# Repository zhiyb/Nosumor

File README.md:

# USB Mix

Design a small USB keyboard for playing [osu!](https://osu.ppy.sh/): [Blog posts](https://zhiyb.wordpress.com/category/cc/embedded/nosumor/)

In addition to mandatory keyboard functionalities, USB audio and Micro SD support are also added. So it's now called USB Mix.

The PCB layout was made compatible with [the original Nosumor v3 casing](http://noodlefighter.com/工作日志/log_nono/), which sells on [the official osu! store](https://osu.ppy.sh/store/product/20).

However, as a hobby project for learning USB framework and achieving high performance, the parts used in this design are probably unnecessarily expensive.

## Features

- USB 2.0 high-speed connection with 8kHz polling rate
- 5 switches (2x Cherry MX switches & 3x tactile switches)
- RGB lighting!
- Audio output through headphone jack using USB audio class 2
- Micro SD card reader
- Application for dynamic reconfiguration and firmware upgrade

### Planned features

- Audio input (MIC) through headphone jack
- MPU-9250 9-axis motion sensor
- ADC waveform capture
- DAC waveform generation

## PCB features

- 50×50 (mm) board area
- 2 mechanical keyboard switches (Cherry MX RGB compatible) and 3 tactile buttons
- Keycap and bottom-side RGB lighting
- STM32F722RE Cortex-M7 high performance MCU @216MHz
- USB 2.0 high-speed PHY USB3370
- 3.5mm audio jack with TLV320AIC3110 audio codec
- InvenSense MPU-9250 9-axis motion sensor
- On-board FT2232D connected to UART & JTAG for debugging
- Test points for 2xADC & 1xDAC
- Extension UART port with 3.3V power

Gerber files for PCB manufacturer Seeed Studio provided.

## Estimated costs

Configuration | Cost
---|---
Basic keyboard | £20
With audio and Micro SD slot | £30
Also with debugging USB port | £38

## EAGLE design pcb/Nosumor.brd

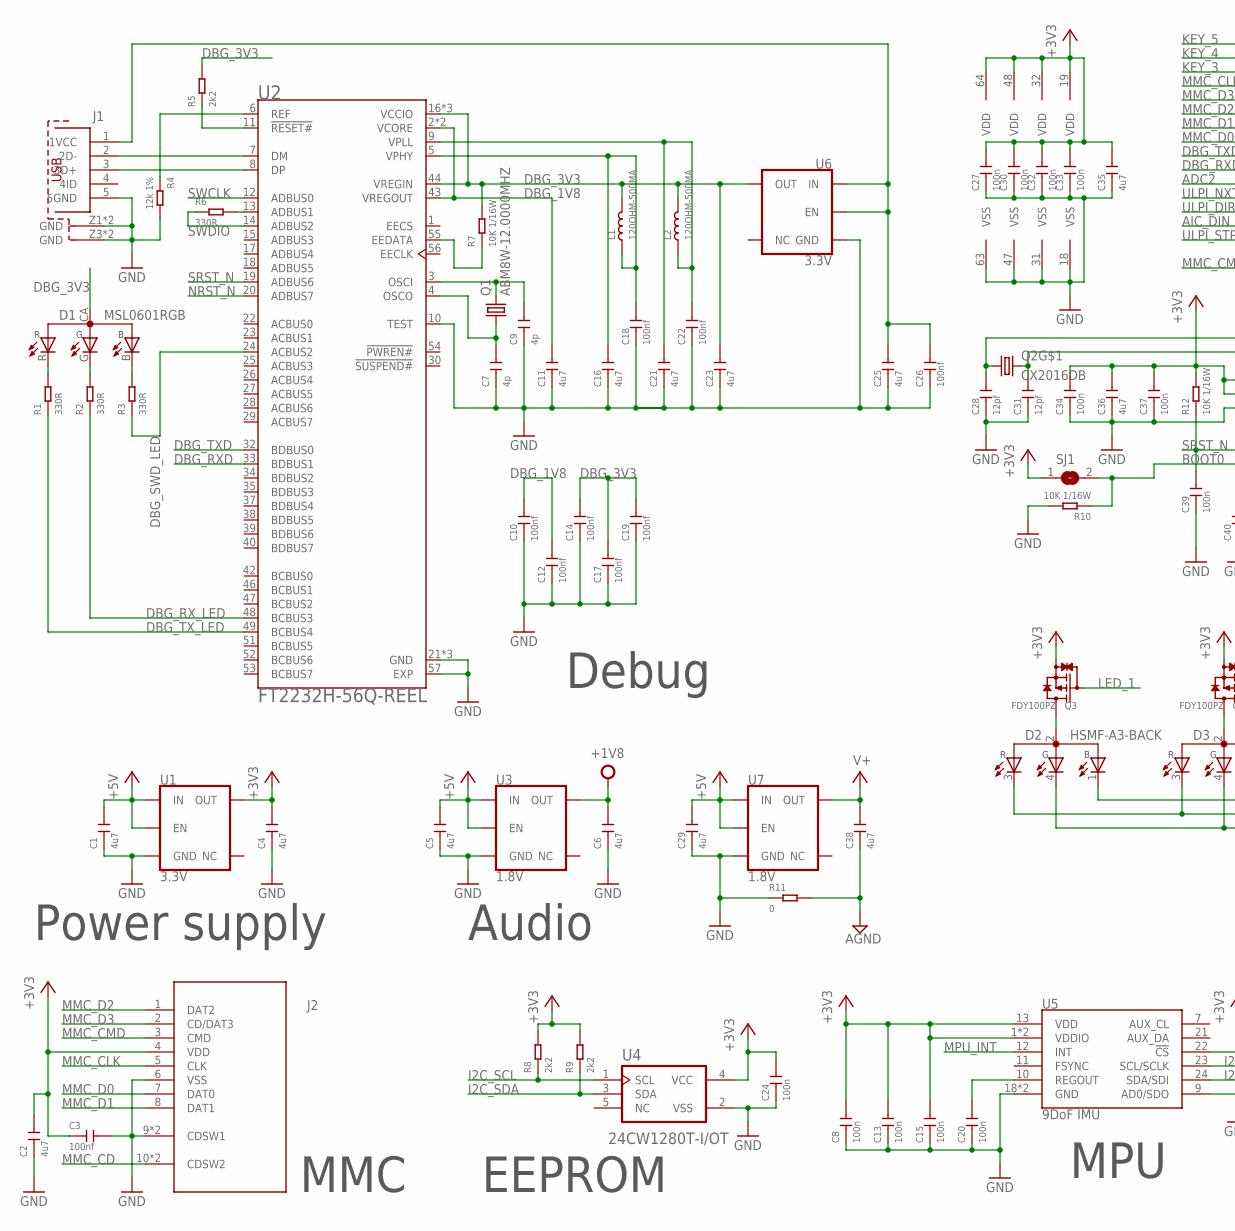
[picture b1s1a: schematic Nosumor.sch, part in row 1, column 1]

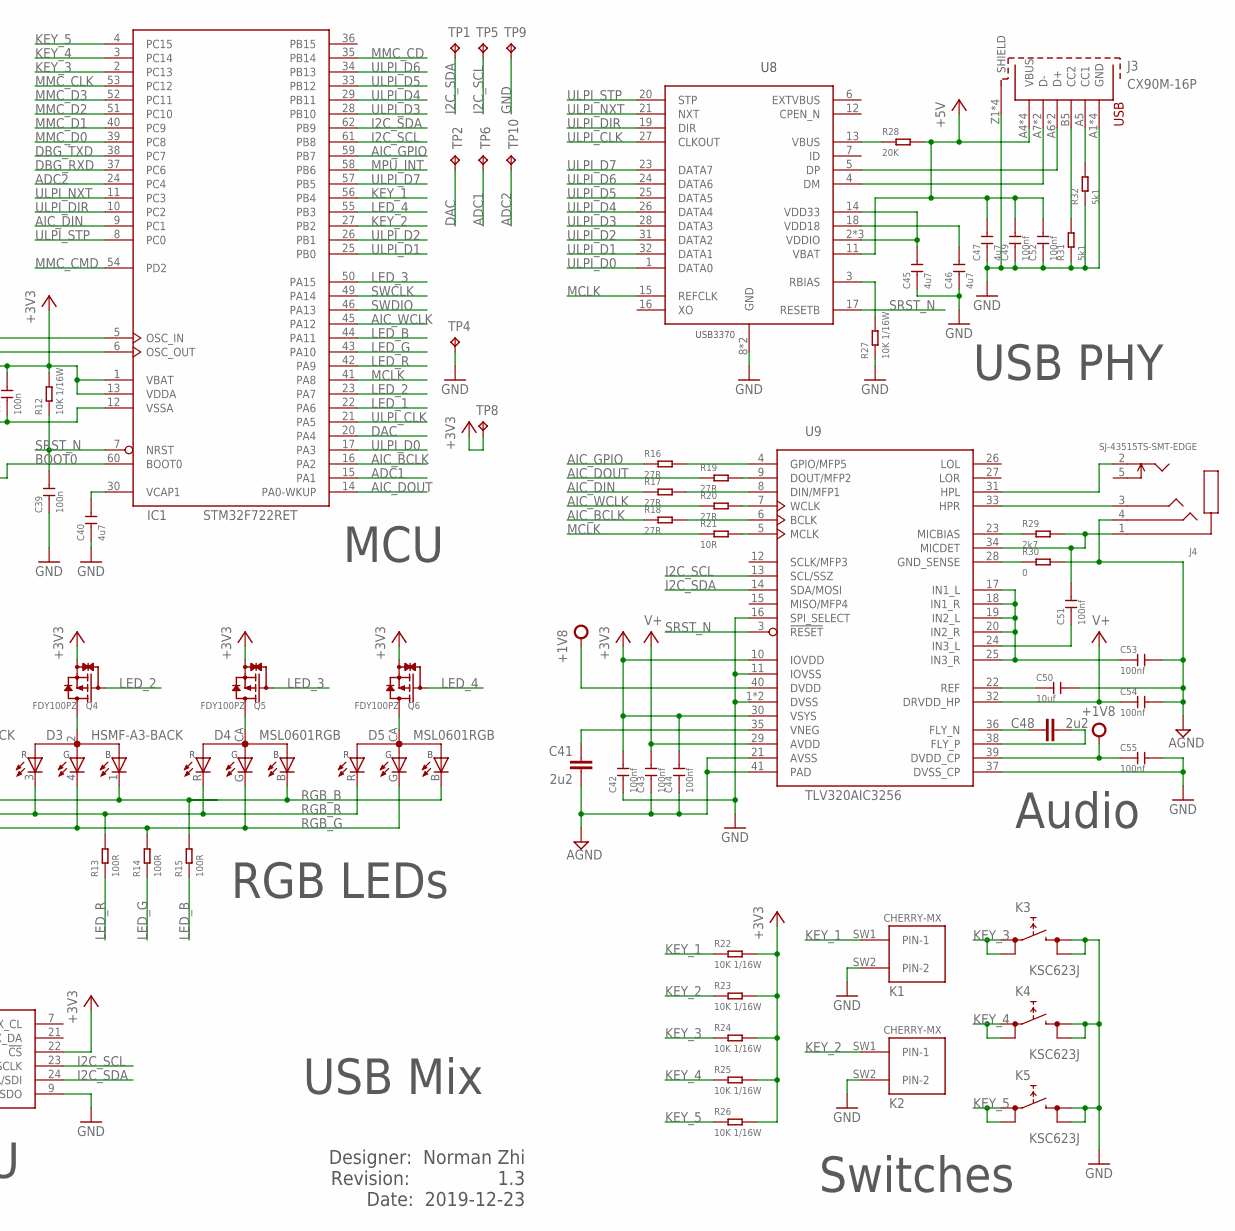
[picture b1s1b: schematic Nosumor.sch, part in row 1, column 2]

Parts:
C1, C2, C4, C5, C6, C11, C16, C21, C23, C25, C29, C38, C45, C46, C47: 4u7; C0402
C3, C10, C12, C14, C17, C18, C19, C22, C26, C42, C43, C44, C49, C51, C52, C53, C54, C55: 100nf; C0402
C7, C9: 4p; C0402
C8, C13, C15, C20, C24, C27, C30, C32, C33, C34, C37, C39: 100n; C0402
C28, C31: 12pf; C0402
C35, C36, C40: 4u7; C0603
C41, C48: 2u2; C0603K
C50: 10uf; C0603
D1, D4, D5: MSL0601RGB; 1105
D2, D3: HSMF-A3-BACK
IC1: STM32F722RET; LQFP64
J1: 629105150521
J2: 693071010811
J3: CX90M-16P
J4: SJ-43515TS-SMT-EDGE; SJ-4351*-SMT-MIRRORED-EDGE
K1, K2: CHERRY-MX
K3, K4, K5: KSC623J; KSC-J
L1, L2: 120OHM-500MA; L0603
Q1: ABM8W-12.0000MHZ; ABM8W
Q2: CX2016DB
Q3, Q4, Q5, Q6: FDY100PZ; SC-89
R1, R2, R3, R6: 330R; R0402
R4: 12k 1%; R0402
R5, R8, R9: 2k2; R0402
R7, R10, R12, R22, R23, R24, R25, R26, R27: 10K 1/16W; R0402
R11, R30: 0; R0402
R13, R14, R15: 100R; R0402
R16, R17, R18, R19, R20: 27R; R0402
R21: 10R; R0402
R28: 20K; R0402
R29: 2k7; R0402
R31, R32: 5k1; R0402
SJ1: SJ
TP1, TP2, TP4, TP5, TP6, TP8, TP9, TP10: TPB1,27; B1,27
U1, U6: 3.3V; SOT23-5
U2: FT2232H-56Q-REEL; QFN50P800X800X100-57N
U3, U7: 1.8V; SOT23-5
U4: 24CW1280T-I/OT; SOT95P280X145-5N
U5: 9DoF IMU; QFN24-3X3
U8: USB3370; QFN32
U9: TLV320AIC3256; QFN40P500X500X80-41N

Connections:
+1V8: C6.2, C55.1, U3.5 (OUT), U9.39 (DVDD_CP), U9.40 (DVDD)
+3V3: C2.2, C3.1, C4.2, C8.2, C13.2, C15.2, C24.2, C27.2, C30.2, C32.2, C33.2, C34.2, C35.2, C36.2, C37.2, C42.2, C44.2, IC1.1 (VBAT), IC1.13 (VDDA), IC1.19 (VDD), IC1.32 (VDD), IC1.48 (VDD), IC1.64 (VDD), J2.4 (VDD), Q3.3 (S), Q4.3 (S), Q5.3 (S), Q6.3 (S), R8.2, R9.2, R12.2, R22.2, R23.2, R24.2, R25.2, R26.2, SJ1.1, TP8.TP, U1.5 (OUT), U4.4 (VCC), U5.1 (VDDIO), U5.8 (VDDIO), U5.13 (VDD), U5.22 (!CS), U9.10 (IOVDD), U9.30 (VSYS)
+5V: C1.2, C5.2, C29.2, C47.2, C49.2, C52.2, J3.A4 (VBUS), J3.A9 (VBUS), J3.B4 (VBUS), J3.B9 (VBUS), R28.2, U1.1 (IN), U1.3 (EN), U3.1 (IN), U3.3 (EN), U7.1 (IN), U7.3 (EN), U8.11 (VBAT)
ADC1: IC1.15 (PA1), TP6.TP
ADC2: IC1.24 (PC4), TP10.TP
AGND: C38.1, C41.2, C43.1, C44.1, C50.2, C53.2, C54.2, J4.4, R11.2, R30.2, U9.21 (AVSS), U9.41 (PAD)
AIC_BCLK: IC1.16 (PA2), R18.1
AIC_BCLK_R: R18.2, U9.6 (BCLK)
AIC_DIN: IC1.9 (PC1), R17.1
AIC_DIN_R: R17.2, U9.8 (DIN/MFP1)
AIC_DOUT: IC1.14 (PA0-WKUP), R19.1
AIC_DOUT_R: R19.2, U9.9 (DOUT/MFP2)
AIC_GPIO: IC1.59 (PB7), R16.1
AIC_GPIO_R: R16.2, U9.4 (GPIO/MFP5)
AIC_MCLK_R: R21.2, U9.5 (MCLK)
AIC_WCLK: IC1.45 (PA12), R20.1
AIC_WCLK_R: R20.2, U9.7 (WCLK)
AVDD: C38.2, C43.2, C54.1, U7.5 (OUT), U9.29 (AVDD), U9.32 (DRVDD_HP)
BOOT0: IC1.60 (BOOT0), R10.1, SJ1.2
DAC: IC1.20 (PA4), TP2.TP
DBG_1V8: C10.2, C11.2, C12.2, U2.2 (VCORE), U2.31 (VCORE), U2.43 (VREGOUT)
DBG_3V3: C14.2, C17.2, C19.2, C23.2, D1.CA (A), L1.2, L2.2, R5.2, R7.2, U2.16 (VCCIO), U2.36 (VCCIO), U2.44 (VREGIN), U2.50 (VCCIO), U6.5 (OUT)
DBG_DM: J1.2 (2D-), U2.7 (DM)
DBG_DP: J1.3 (3D+), U2.8 (DP)
DBG_RXD: IC1.37 (PC6), U2.33 (BDBUS1)
DBG_RX_LED: R2.1, U2.48 (BCBUS3)
DBG_SWD_LED: R3.1, U2.24 (ACBUS2)
DBG_TXD: IC1.38 (PC7), U2.32 (BDBUS0)
DBG_TX_LED: R1.1, U2.49 (BCBUS4)
GND: C1.1, C2.1, C3.2, C4.1, C5.1, C6.1, C7.1, C8.1, C9.1, C10.1, C11.1, C12.1, C13.1, C14.1, C15.1, C16.1, C17.1, C18.1, C19.1, C20.1, C21.1, C22.1, C23.1, C24.1, C25.1, C26.1, C27.1, C28.1, C29.1, C30.1, C31.1, C32.1, C33.1, C34.1, C35.1, C36.1, C37.1, C39.1, C40.1, C42.1, C45.1, C46.1, C47.1, C49.1, C52.1, C55.2, IC1.12 (VSSA), IC1.18 (VSS), IC1.31 (VSS), IC1.47 (VSS), IC1.63 (VSS), J1.5 (5GND), J1.Z1 (GND), J1.Z2 (GND), J1.Z3 (GND), J1.Z4 (GND), J2.6 (VSS), J2.9 (CDSW1), J2.9-1 (CDSW1), J3.A1 (GND), J3.A12 (GND), J3.B1 (GND), J3.B12 (GND), J3.Z1 (SHIELD), J3.Z2 (SHIELD), J3.Z3 (SHIELD), J3.Z4 (SHIELD), K1.SW2 (PIN-2), K2.SW2 (PIN-2), K3.2, K3.4 (2), K4.2, K4.4 (2), K5.2, K5.4 (2), Q2.2 (GND), R4.2, R10.2, R11.1, R27.1, R31.1, R32.1, TP4.TP, TP9.TP, U1.2 (GND), U2.10 (TEST), U2.21 (GND), U2.41 (GND), U2.45 (GND), U2.57 (EXP), U3.2 (GND), U4.2 (VSS), U5.9 (AD0/SDO), U5.18 (GND), U5.20 (GND), U6.2 (GND), U7.2 (GND), U8.8 (GND), U8.EXP (GND), U9.1 (DVSS), U9.2 (DVSS), U9.11 (IOVSS), U9.16 (SPI_SELECT), U9.37 (DVSS_CP)
I2C_SCL: IC1.61 (PB8), R8.1, TP5.TP, U4.1 (SCL), U5.23 (SCL/SCLK), U9.13 (SCL/SSZ)
I2C_SDA: IC1.62 (PB9), R9.1, TP1.TP, U4.3 (SDA), U5.24 (SDA/SDI), U9.14 (SDA/MOSI)
KEY_1: IC1.56 (PB4), K1.SW1 (PIN-1), R22.1
KEY_2: IC1.27 (PB2), K2.SW1 (PIN-1), R23.1
KEY_3: IC1.2 (PC13), K3.1, K3.3 (1), R24.1
KEY_4: IC1.3 (PC14), K4.1, K4.3 (1), R25.1
KEY_5: IC1.4 (PC15), K5.1, K5.3 (1), R26.1
LED_1: IC1.22 (PA6), Q3.1 (G)
LED_2: IC1.23 (PA7), Q4.1 (G)
LED_3: IC1.50 (PA15), Q5.1 (G)
LED_4: IC1.55 (PB3), Q6.1 (G)
LED_B: IC1.44 (PA11), R15.1
LED_G: IC1.43 (PA10), R14.1
LED_R: IC1.42 (PA9), R13.1
MCLK: IC1.41 (PA8), R21.1, U8.15 (REFCLK)
MMC_CD: IC1.35 (PB14), J2.10 (CDSW2), J2.10-1 (CDSW2)
MMC_CLK: IC1.53 (PC12), J2.5 (CLK)
MMC_CMD: IC1.54 (PD2), J2.3 (CMD)
MMC_D0: IC1.39 (PC8), J2.7 (DAT0)
MMC_D1: IC1.40 (PC9), J2.8 (DAT1)
MMC_D2: IC1.51 (PC10), J2.1 (DAT2)
MMC_D3: IC1.52 (PC11), J2.2 (CD/DAT3)
MPU_INT: IC1.58 (PB6), U5.12 (INT)
unnamed: J3.A5 (CC1), R32.2
unnamed: J3.A7 (D-), J3.B7 (D-), U8.4 (DM)
unnamed: J3.A6 (D+), J3.B6 (D+), U8.5 (DP)
unnamed: J3.B5 (CC2), R31.2
unnamed: C9.2, Q1.P$3 (2), U2.3 (OSCI)
unnamed: C7.2, Q1.P$1 (1), U2.4 (OSCO)
unnamed: C51.1, U9.24 (IN3_L)
unnamed: D4.CA (A), Q5.2 (D)
unnamed: J4.3, U9.33 (HPR)
unnamed: J4.2, U9.31 (HPL)
unnamed: R7.1, U2.55 (EEDATA)
unnamed: D1.R (KR), R1.2
unnamed: C51.2, J4.1, R29.2, U9.34 (MICDET)
unnamed: R29.1, U9.23 (MICBIAS)
unnamed: R30.1, U9.28 (GND_SENSE)
unnamed: C53.1, U9.17 (IN1_L), U9.18 (IN1_R), U9.19 (IN2_L), U9.20 (IN2_R), U9.25 (IN3_R)
unnamed: C50.1, U9.22 (REF)
unnamed: C48.1, U9.36 (FLY_N)
unnamed: C28.2, IC1.5 (OSC_IN), Q2.1
unnamed: C48.2, U9.38 (FLY_P)
unnamed: C31.2, IC1.6 (OSC_OUT), Q2.3 (2)
unnamed: D5.CA (A), Q6.2 (D)
unnamed: C40.2, IC1.30 (VCAP1)
unnamed: D1.G (KG), R2.2
unnamed: R28.1, U8.13 (VBUS)
unnamed: D2.2 (A), Q3.2 (D)
unnamed: R27.2, U8.3 (RBIAS)
unnamed: C41.1, U9.35 (VNEG)
unnamed: D3.2 (A), Q4.2 (D)
unnamed: D1.B (KB), R3.2
unnamed: C25.2, C26.2, J1.1 (1VCC), U6.1 (IN), U6.3 (EN)
unnamed: C20.2, U5.10 (REGOUT)
unnamed: R4.1, U2.6 (REF)
unnamed: R5.1, U2.11 (!RESET#)
unnamed: C16.2, C18.2, L1.1, U2.5 (VPHY)
unnamed: C21.2, C22.2, L2.1, U2.9 (VPLL)
unnamed: R6.2, U2.13 (ADBUS1)
NRST_N: U2.20 (ADBUS7)
RGB_B: D2.1 (KB), D3.1 (KB), D4.B (KB), D5.B (KB), R15.2
RGB_G: D2.4 (KG), D3.4 (KG), D4.G (KG), D5.G (KG), R14.2
RGB_R: D2.3 (KR), D3.3 (KR), D4.R (KR), D5.R (KR), R13.2
SRST_N: C39.2, IC1.7 (NRST), R12.1, U2.19 (ADBUS6), U8.17 (RESETB), U9.3 (!RESET)
SWCLK: IC1.49 (PA14), U2.12 (ADBUS0)
SWDIO: IC1.46 (PA13), R6.1, U2.14 (ADBUS2)
ULPI_CLK: IC1.21 (PA5), U8.27 (CLKOUT)
ULPI_D0: IC1.17 (PA3), U8.1 (DATA0)
ULPI_D1: IC1.25 (PB0), U8.32 (DATA1)
ULPI_D2: IC1.26 (PB1), U8.31 (DATA2)
ULPI_D3: IC1.28 (PB10), U8.28 (DATA3)
ULPI_D4: IC1.29 (PB11), U8.26 (DATA4)
ULPI_D5: IC1.33 (PB12), U8.25 (DATA5)
ULPI_D6: IC1.34 (PB13), U8.24 (DATA6)
ULPI_D7: IC1.57 (PB5), U8.23 (DATA7)
ULPI_DIR: IC1.10 (PC2), U8.19 (DIR)
ULPI_NXT: IC1.11 (PC3), U8.21 (NXT)
ULPI_STP: IC1.8 (PC0), U8.20 (STP)
VUSB18: C46.2, U8.18 (VDD18)
VUSB33: C45.2, U8.2 (VDDIO), U8.14 (VDD33), U8.22 (VDDIO), U8.30 (VDDIO)

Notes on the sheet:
Debug
Switches
Power supply
MMC
USB PHY
Audio
MCU
RGB LEDs
MPU
EEPROM
Designer: Norman Zhi Revision: 1.3 Date: 2019-12-23
USB Mix

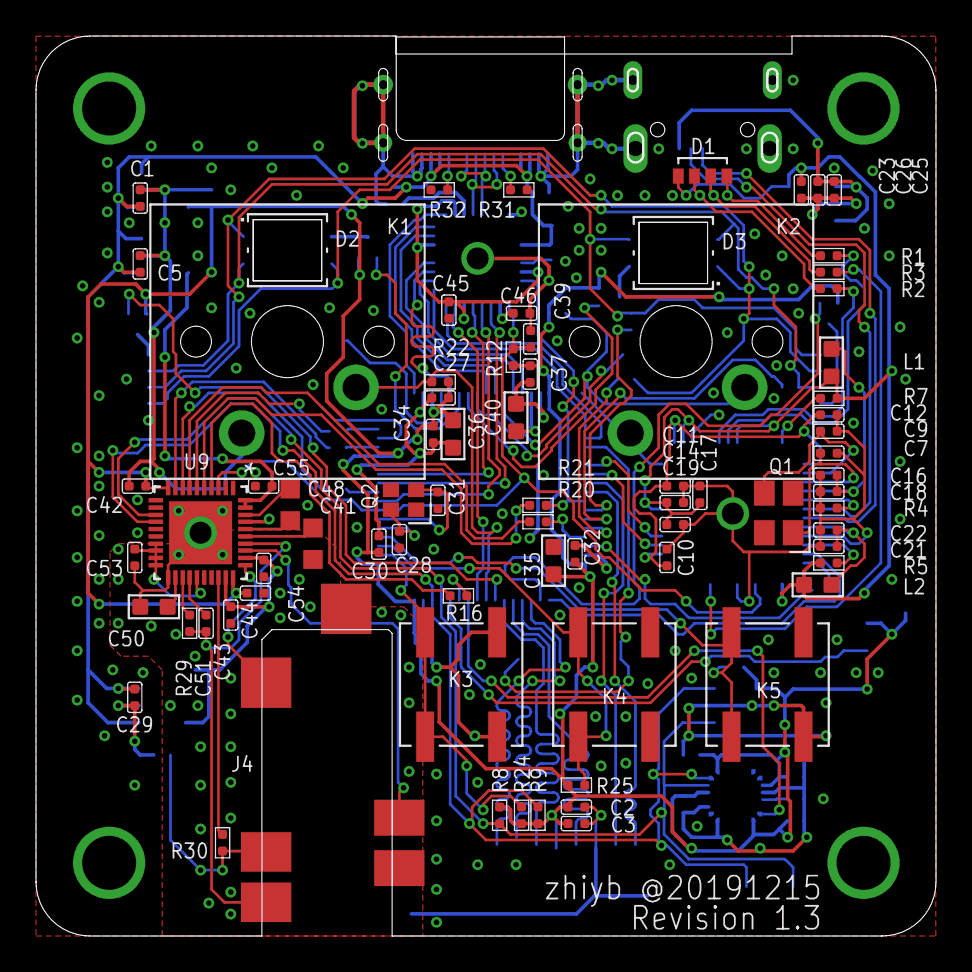
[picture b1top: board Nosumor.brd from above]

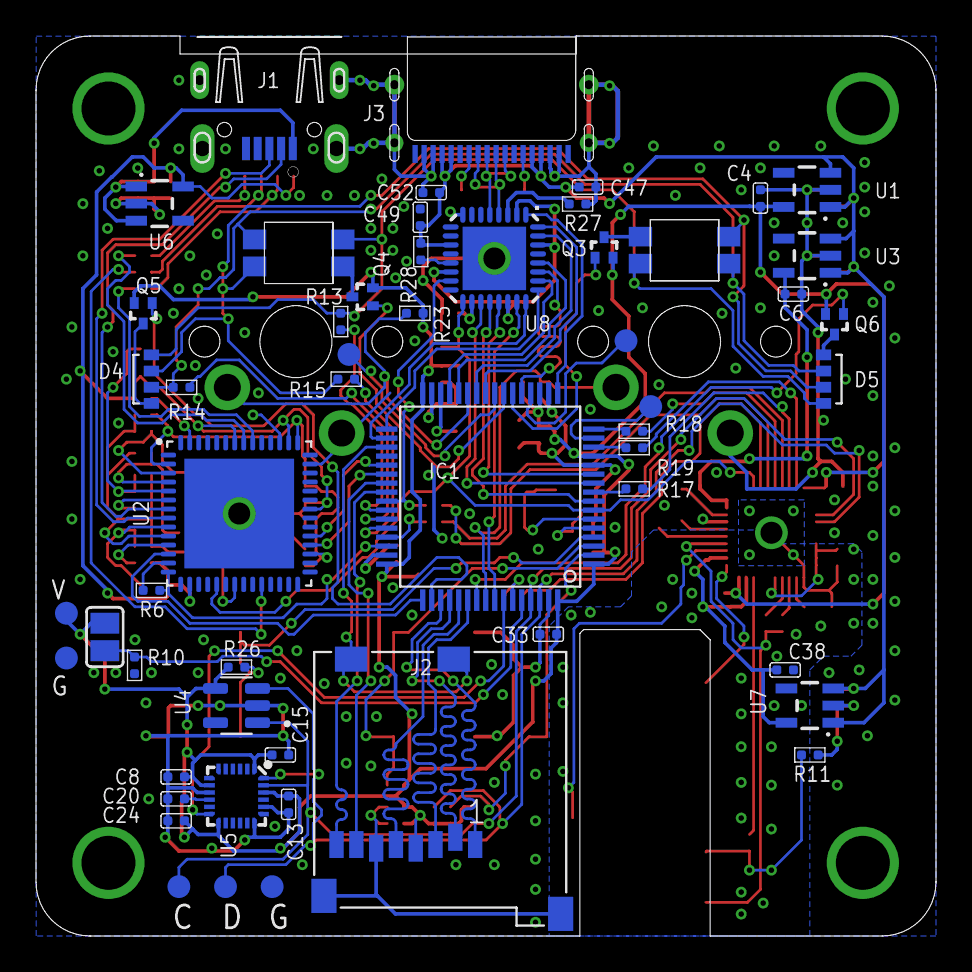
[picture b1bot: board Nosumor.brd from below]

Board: 2 copper layers, 50.0 x 50.0 mm, 128 parts (52 on the bottom side), 110 nets.

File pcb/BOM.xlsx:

Section | Type | Value | Designator | Part # | Quantity | Unit Price | Link
Audio | Capacitor | 100n | C42, C43, C44, C51, C53, C54, C55 | CC0402KRX7R7BB104 | 7 | 8.9999999999999993E-3 | https://www.mouser.co.uk/ProductDetail/603-CC402KRX7R7BB104
Audio | Capacitor | 10u | C50 | GRM188R60J106ME47D | 1 | 0.218 | https://www.mouser.co.uk/productdetail/81-grm188r60j106me47
Audio | Capacitor | 2u2 | C41, C48 | C1608X7R1A225K080AC | 2 | 0.14799999999999999 | https://www.mouser.co.uk/ProductDetail/810-C1608X7R1A225K
Audio | Capacitor | 4u7 | C5, C6, C29, C38 | GRM155R61A475MEAAD | 4 | 6.6000000000000003E-2 | https://www.mouser.co.uk/ProductDetail/81-GRM155R61A475MEAD
Audio | Connector | 3.5mm Jack | J4 | SJ-43515TS-SMT-TR | 1 | 0.81599999999999995 | https://www.mouser.co.uk/ProductDetail/490-SJ43515TS-SMT-TR
Audio | IC | AP2112K-1.8V | U3, U7 | AP2112K-1.8TRG1 | 2 | 0.25 | https://www.mouser.co.uk/ProductDetail/621-AP2112K-1.8TRG1
Audio | IC | TLV320AIC3256 | U9 | TLV320AIC3256IRSBT | 1 | 8.5299999999999994 | https://www.mouser.co.uk/ProductDetail/595-V320AIC3256IRSBT
Audio | Resistor | 0R | R11, R30 | RC0402FR-070RL | 2 | 3.0000000000000001E-3 | https://www.mouser.co.uk/ProductDetail/603-RC0402FR-070RL
Audio | Resistor | 10R | R21 | RC0402FR-0710RL | 1 | 4.0000000000000001E-3 | https://www.mouser.co.uk/ProductDetail/Yageo/RC0402FR-0710RL
Audio | Resistor | 27R | R16, R17, R18, R19, R20 | RC0402FR-0727RL | 5 | 3.0000000000000001E-3 | https://www.mouser.co.uk/ProductDetail/603-RC0402FR-0727RL
Audio | Resistor | 2k7 | R29 | RC0402FR-072K7L | 1 | 3.0000000000000001E-3 | https://www.mouser.co.uk/ProductDetail/603-RC0402FR-072K7L
Basic | Capacitor | 100n | C27, C30, C32, C33, C34, C37, C39, C49, C52 | CC0402KRX7R7BB104 | 9 | 8.9999999999999993E-3 | https://www.mouser.co.uk/ProductDetail/603-CC402KRX7R7BB104
Basic | Capacitor | 12p | C28, C31 | GRM1555C1H120JA01D | 2 | 3.1E-2 | https://www.mouser.co.uk/productdetail/81-grm1555c1h120ja1d
Basic | Capacitor | 4u7 | C1, C4, C35, C36, C40, C45, C46, C47 | GRM155R61A475MEAAD | 8 | 6.6000000000000003E-2 | https://www.mouser.co.uk/ProductDetail/81-GRM155R61A475MEAD
Basic | Connector | USB Type-C | J3 | CX90M-16P | 1 | 1.75 | https://www.mouser.co.uk/ProductDetail/798-CX90M-16P
Basic | Crystal | 19.2M | Q2 | CX2016DB19200H0FLJC2 | 1 | 0.46100000000000002 | https://www.mouser.co.uk/ProductDetail/581-CX2016DB19200HLJ
Basic | IC | AP2112K-3.3V | U1 | AP2112K-3.3TRG1 | 1 | 0.25 | https://www.mouser.co.uk/ProductDetail/621-AP2112K-3.3TRG1
Basic | IC | STM32F722 | IC1 | STM32F722RET6 | 1 | 7.9 | https://www.mouser.co.uk/ProductDetail/511-STM32F722RET6
Basic | IC | USB3370B | U8 | USB3370B-EZK-TR | 1 | 1.21 | https://www.mouser.co.uk/productdetail/886-usb3370b-ezk-tr
Basic | LED | RGB | D2, D3 | ASMB-MTB1-0A3A2 | 2 | 0.27400000000000002 | https://uk.rs-online.com/web/p/visible-leds/8305079/
Basic | LED | RGB Sideway | D4, D5 | MSL0601RGBU1 | 2 | 0.67300000000000004 | https://www.mouser.co.uk/ProductDetail/755-MSL0601RGBU1
Basic | MOSFET | P-Channel | Q3, Q4, Q5, Q6 | FDY100PZ | 4 | 0.23 | https://www.mouser.co.uk/ProductDetail/512-FDY100PZ
Basic | Resistor | 100R | R13, R14, R15 | RC0402FR-07100RL | 3 | 3.0000000000000001E-3 | https://www.mouser.co.uk/ProductDetail/603-RC0402FR-07100RL
Basic | Resistor | 10k | R10, R12, R22, R23, R24, R25, R26, R27 | RC0402FR-0710KL | 8 | 3.0000000000000001E-3 | https://www.mouser.co.uk/productdetail/603-rc0402fr-0710kl
Basic | Resistor | 20k | R28 | RC0402FR-0720KL | 1 | 3.0000000000000001E-3 | https://www.mouser.co.uk/productdetail/603-rc0402fr-0720kl
Basic | Resistor | 2k2 | R8, R9 | RC0402FR-072K2L | 2 | 3.0000000000000001E-3 | https://www.mouser.co.uk/productdetail/603-rc0402fr-072k2l
Basic | Resistor | 5k1 | R31, R32 | RC0402FR-075K1L | 2 | 3.0000000000000001E-3 | https://www.mouser.co.uk/ProductDetail/603-RC0402FR-075K1L
Basic | Switch | Cherry-MX | K1, K2 |  | 2 | 1
Basic | Switch | Tactile | K3, K4, K5 | KSC623JLFG | 3 | 0.72199999999999998 | https://www.mouser.co.uk/ProductDetail/611-KSC623JLFG
Debug | Capacitor | 100n | C10, C12, C14, C17, C18, C19, C22, C26 | CC0402KRX7R7BB104 | 8 | 8.9999999999999993E-3 | https://www.mouser.co.uk/ProductDetail/603-CC402KRX7R7BB104
Debug | Capacitor | 4p | C7, C9 | GJM1555C1H4R0BB01D | 2 | 0.1 | https://www.mouser.co.uk/ProductDetail/81-GJM1555C1H4R0BB01
Debug | Capacitor | 4u7 | C11, C16, C21, C23, C25 | GRM155R61A475MEAAD | 5 | 6.6000000000000003E-2 | https://www.mouser.co.uk/ProductDetail/81-GRM155R61A475MEAD
Debug | Connector | USB Micro-B | J1 | 629105150521 | 1 | 1.65 | https://www.mouser.co.uk/ProductDetail/710-629105150521
Debug | Crystal | 12M | Q1 | ABM8W-12.0000MHZ-4-D1X-T3 | 1 | 0.58699999999999997 | https://www.mouser.co.uk/ProductDetail/815-8W12-4D1XT
Debug | IC | AP2112K-3.3V | U6 | AP2112K-3.3TRG1 | 1 | 0.25 | https://www.mouser.co.uk/ProductDetail/621-AP2112K-3.3TRG1
Debug | IC | FT2232H | U2 | FT2232H-56Q-TRAY | 1 | 4.43 | https://www.mouser.co.uk/ProductDetail/895-FT2232H-56Q-TRAY
Debug | Inductor | 120R/500mA | L1, L2 | BLM18AG121BH1D | 2 | 3.3000000000000002E-2 | https://www.mouser.co.uk/ProductDetail/81-BLM18AG121BH1D
Debug | LED | RGB Sideway | D1 | MSL0601RGBU1 | 1 | 0.67300000000000004 | https://www.mouser.co.uk/ProductDetail/755-MSL0601RGBU1
Debug | Resistor | 10k | R7 | RC0402FR-0710KL | 1 | 3.0000000000000001E-3 | https://www.mouser.co.uk/productdetail/603-rc0402fr-0710kl
Debug | Resistor | 12k 1% | R4 | RC0402FR-1312KL | 1 | 3.0000000000000001E-3 | https://www.mouser.co.uk/ProductDetail/603-RC0402FR-1312KL
Debug | Resistor | 2k2 | R5 | RC0402FR-072K2L | 1 | 3.0000000000000001E-3 | https://www.mouser.co.uk/productdetail/603-rc0402fr-072k2l
Debug | Resistor | 330R | R1, R2, R3, R6 | RC0402FR-07330RL | 4 | 3.0000000000000001E-3 | https://www.mouser.co.uk/productdetail/603-rc0402fr-07330rl
EEPROM | Capacitor | 100n | C24 | CC0402KRX7R7BB104 | 1 | 8.9999999999999993E-3 | https://www.mouser.co.uk/ProductDetail/603-CC402KRX7R7BB104
EEPROM | IC | 24CW1280T | U4 | 24CW1280T-I/OT | 1 | 0.35099999999999998 | https://www.mouser.co.uk/ProductDetail/579-24CW1280T-I-OT
MMC | Capacitor | 100n | C3 | CC0402KRX7R7BB104 | 1 | 8.9999999999999993E-3 | https://www.mouser.co.uk/ProductDetail/603-CC402KRX7R7BB104
MMC | Capacitor | 4u7 | C2 | GRM155R61A475MEAAD | 1 | 6.6000000000000003E-2 | https://www.mouser.co.uk/ProductDetail/81-GRM155R61A475MEAD
MMC | Connector | Micro SD | J2 | 693071010811 | 1 | 2.3199999999999998 | https://www.mouser.co.uk/ProductDetail/710-693071010811
MPU | Capacitor | 100n | C8, C13, C15, C20 | CC0402KRX7R7BB104 | 4 | 8.9999999999999993E-3 | https://www.mouser.co.uk/ProductDetail/603-CC402KRX7R7BB104
MPU | IC | MPU9250 | U5 | MPU-9250 | 1 | 7.13
Total |  |  |  |  | 119 | 48.185000000000016

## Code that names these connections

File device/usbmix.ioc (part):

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PC3.Mode=Ext_Phy_OTG/Dual-Role-Device
PH0-OSC_IN.Signal=RCC_OSC_IN
Mcu.UserName=STM32F722RETx
PB10.Mode=Ext_Phy_OTG/Dual-Role-Device
PC10.Signal=SDMMC1_D2
PC12.Signal=SDMMC1_CK
PB11.Signal=USB_OTG_HS_ULPI_D4
PB13.Signal=USB_OTG_HS_ULPI_D6
RCC.SYSCLKSource=RCC_SYSCLKSOURCE_PLLCLK
PA12.Signal=SAI2_FS_B
PB6.Signal=GPXTI6
PC7.Signal=USART6_RX
PC3.Signal=USB_OTG_HS_ULPI_NXT
PA8.GPIOParameters=GPIO_Speed
PH0-OSC_IN.Mode=HSE-External-Oscillator
RCC.HSE_VALUE=19200000
PB2.Signal=GPXTI2
PA14.Mode=Serial_Wire
PB5.Mode=Ext_Phy_OTG/Dual-Role-Device
PC9.Mode=SD_4_bits_Wide_bus
PB7.Signal=GPXTI7
PA8.Signal=RCC_MCO_1
PH1-OSC_OUT.Mode=HSE-External-Oscillator
Mcu.Package=LQFP64
PB9.Signal=I2C1_SDA
PB1.Signal=USB_OTG_HS_ULPI_D2
PA6.Signal=S_TIM3_CH1
PB12.Mode=Ext_Phy_OTG/Dual-Role-Device
PA10.Signal=S_TIM1_CH3
PA15.Signal=S_TIM2_CH1_ETR
PC11.Mode=SD_4_bits_Wide_bus
PB13.Mode=Ext_Phy_OTG/Dual-Role-Device
PA8.GPIO_Speed=GPIO_SPEED_FREQ_VERY_HIGH
PB4.Signal=GPXTI4
PA3.Signal=USB_OTG_HS_ULPI_D0
PA5.Mode=Ext_Phy_OTG/Dual-Role-Device
PC11.Signal=SDMMC1_D3
PC13.Signal=GPXTI13
PC8.Signal=SDMMC1_D0
PC2.Signal=USB_OTG_HS_ULPI_DIR
PC4.Signal=ADCx_IN14
PC6.Signal=USART6_TX
PC10.Mode=SD_4_bits_Wide_bus
PC2.Mode=Ext_Phy_OTG/Dual-Role-Device
PC0.Signal=USB_OTG_HS_ULPI_STP
PC14-OSC32_IN.Signal=GPXTI14
PA0-WKUP.Signal=SAI2_SD_B
PC0.Mode=Ext_Phy_OTG/Dual-Role-Device
PA0-WKUP.Mode=SAI_B_AsyncSlave
PA3.Mode=Ext_Phy_OTG/Dual-Role-Device
PA13.Signal=SYS_JTMS-SWDIO
PB11.Mode=Ext_Phy_OTG/Dual-Role-Device
PC6.Mode=Asynchronous
PB9.Mode=I2C
PA9.Signal=S_TIM1_CH2
PC15-OSC32_OUT.Signal=GPXTI15
PA1.Signal=ADCx_IN1
PB10.Signal=USB_OTG_HS_ULPI_D3
PB14.Signal=GPIO_Input
PD2.Mode=SD_4_bits_Wide_bus
PA5.Signal=USB_OTG_HS_ULPI_CK
PC12.Mode=SD_4_bits_Wide_bus
PB0.Mode=Ext_Phy_OTG/Dual-Role-Device
board=custom
PH1-OSC_OUT.Signal=RCC_OSC_OUT
PA13.Mode=Serial_Wire
Mcu.Name=STM32F722R(C-E)Tx
PA2.Signal=SAI2_SCK_B
PC8.Mode=SD_4_bits_Wide_bus
PB3.Signal=S_TIM2_CH2
PA4.Signal=COMP_DAC1_group
RCC.SYSCLKFreq_VALUE=216000000
PB5.Signal=USB_OTG_HS_ULPI_D7
PA12.Mode=SAI_B_AsyncSlave
PA11.Signal=S_TIM1_CH4
PA14.Signal=SYS_JTCK-SWCLK
PB1.Mode=Ext_Phy_OTG/Dual-Role-Device
PB8.Mode=I2C
PA2.Mode=SAI_B_AsyncSlave
PB8.Signal=I2C1_SCL
PA8.Mode=Clock-out-1
PC9.Signal=SDMMC1_D1
PC7.Mode=Asynchronous
PD2.Signal=SDMMC1_CMD
PB0.Signal=USB_OTG_HS_ULPI_D1
PC1.Signal=SAI1_SD_A
PB12.Signal=USB_OTG_HS_ULPI_D5
PC1.Mode=SAI_A_SPDIF
PA7.Signal=S_TIM3_CH2

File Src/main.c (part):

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  /* USER CODE BEGIN 3 */
    HAL_GPIO_WritePin(LED_GPIO, LED_LEFT, HAL_GPIO_ReadPin(KEY_GPIO, KEY_LEFT) ? GPIO_PIN_RESET : GPIO_PIN_SET);
    HAL_GPIO_WritePin(LED_GPIO, LED_RIGHT, HAL_GPIO_ReadPin(KEY_GPIO, KEY_RIGHT) ? GPIO_PIN_RESET : GPIO_PIN_SET);
    HAL_GPIO_WritePin(LED_GPIO, LED_RED, HAL_GPIO_ReadPin(KEY_GPIO, KEY_1) ? GPIO_PIN_RESET : GPIO_PIN_SET);
    HAL_GPIO_WritePin(LED_GPIO, LED_GREEN, HAL_GPIO_ReadPin(KEY_GPIO, KEY_2) ? GPIO_PIN_RESET : GPIO_PIN_SET);
    HAL_GPIO_WritePin(LED_GPIO, LED_BLUE, HAL_GPIO_ReadPin(KEY_GPIO, KEY_3) ? GPIO_PIN_RESET : GPIO_PIN_SET);
    if (!HAL_GPIO_ReadPin(KEY_GPIO, KEY_LEFT)) {
      uint8_t report[] = {REPORT_MOUSE, 0, -10, -10, 0};
      USBD_CUSTOM_HID_SendReport_FS(report, sizeof(report));
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      uint8_t report[] = {REPORT_MOUSE, 0, 10, 10, 0};
      USBD_CUSTOM_HID_SendReport_FS(report, sizeof(report));
    }
    if (!HAL_GPIO_ReadPin(KEY_GPIO, KEY_1))
      dbbkpt();
    if (!HAL_GPIO_ReadPin(KEY_GPIO, KEY_2))
      dbsystem("echo Hello, world! test.");
#if 0
    if (!HAL_GPIO_ReadPin(KEY_GPIO, KEY_RIGHT)) {
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        * EXTI
        * Free pins are configured automatically as Analog (this feature is enabled through 
        * the Code Generation settings)
     PA9   ------> USART1_TX
     PA10   ------> USART1_RX
*/
void MX_GPIO_Init(void)
{
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  __HAL_RCC_GPIOA_CLK_ENABLE();
  __HAL_RCC_GPIOB_CLK_ENABLE();

  /*Configure GPIO pins : PC13 PC14 PC15 */
  GPIO_InitStruct.Pin = GPIO_PIN_13|GPIO_PIN_14|GPIO_PIN_15;
  GPIO_InitStruct.Mode = GPIO_MODE_ANALOG;
  HAL_GPIO_Init(GPIOC, &GPIO_InitStruct);

  /*Configure GPIO pins : PA0 PA6 PA7 PA8 
                           PA15 */
  GPIO_InitStruct.Pin = GPIO_PIN_0|GPIO_PIN_6|GPIO_PIN_7|GPIO_PIN_8 
                          |GPIO_PIN_15;
  GPIO_InitStruct.Mode = GPIO_MODE_ANALOG;
  HAL_GPIO_Init(GPIOA, &GPIO_InitStruct);

  /*Configure GPIO pins : PA1 PA2 PA3 PA4 
                           PA5 */
  GPIO_InitStruct.Pin = GPIO_PIN_1|GPIO_PIN_2|GPIO_PIN_3|GPIO_PIN_4 
                          |GPIO_PIN_5;
  GPIO_InitStruct.Mode = GPIO_MODE_OUTPUT_PP;
  GPIO_InitStruct.Speed = GPIO_SPEED_FREQ_MEDIUM;
  HAL_GPIO_Init(GPIOA, &GPIO_InitStruct);

  /*Configure GPIO pins : PB0 PB1 PB2 PB11 
                           PB12 PB3 PB4 PB5 
                           PB6 PB7 PB8 */
  GPIO_InitStruct.Pin = GPIO_PIN_0|GPIO_PIN_1|GPIO_PIN_2|GPIO_PIN_11 
                          |GPIO_PIN_12|GPIO_PIN_3|GPIO_PIN_4|GPIO_PIN_5 
                          |GPIO_PIN_6|GPIO_PIN_7|GPIO_PIN_8;
  GPIO_InitStruct.Mode = GPIO_MODE_ANALOG;
  HAL_GPIO_Init(GPIOB, &GPIO_InitStruct);

  /*Configure GPIO pins : PB10 PB13 PB14 PB15 
                           PB9 */
  GPIO_InitStruct.Pin = GPIO_PIN_10|GPIO_PIN_13|GPIO_PIN_14|GPIO_PIN_15 
                          |GPIO_PIN_9;
  GPIO_InitStruct.Mode = GPIO_MODE_INPUT;
  GPIO_InitStruct.Pull = GPIO_PULLUP;
  HAL_GPIO_Init(GPIOB, &GPIO_InitStruct);

  /*Configure GPIO pin : PA9 */
  GPIO_InitStruct.Pin = GPIO_PIN_9;
  GPIO_InitStruct.Mode = GPIO_MODE_AF_PP;
  GPIO_InitStruct.Speed = GPIO_SPEED_FREQ_HIGH;
  HAL_GPIO_Init(GPIOA, &GPIO_InitStruct);

  /*Configure GPIO pin : PA10 */
  GPIO_InitStruct.Pin = GPIO_PIN_10;
  GPIO_InitStruct.Mode = GPIO_MODE_INPUT;
  GPIO_InitStruct.Pull = GPIO_NOPULL;
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
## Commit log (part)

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2017-06-25 USB HS initial
2017-06-28 USB setup initial
2017-06-29 Audio ADC loopback test
2017-06-29 Sine wave generation for audio testing
2017-07-05 USB Keyboard initial
2017-07-05 String descriptors, USB HID keyboard descriptors
2017-07-06 Keyboard interrupts initial
2017-07-06 Report all 5 keys
2017-07-06 Keyboard report initial
2017-07-06 Fix keyboard debouncing
2017-07-12 Nosumor PCB V0.3 USB audio initial
2017-07-19 SDMMC overclocks to 72MHz (more tests needed)
2017-07-19 Audio codec with DMA transmit initial
2017-07-20 Image of audio codec 192kHz sample frequency clock configuration
2017-07-24 USB Audio volume control initial
2017-07-24 USB implement more requests
2017-07-31 USB HID vendor device
2017-07-31 Host hidapi initial
2017-08-01 SD V2.00 SDSC support
2017-08-01 Host module separation, uses spdlog for logging
2017-08-01 IAP working
2017-08-02 Move flash functions to ITCM RAM
2017-08-10 Fix host HID application on Linux
2017-09-01 USB Audio Class 2 initial
2017-09-07 UAC2 + codec play but noisy
2017-09-08 UAC2 structural update, clock selector initial
2017-09-09 UAC2 reduce noise
2017-09-09 Audio volume display in debug build
2017-09-09 Optimise audio reconfiguration
2017-09-10 USB Audio Class 2 with feedback endpoint
2017-09-11 USB audio structural rewrite
2017-09-11 More detailed panic debugging information
2017-09-12 USB audio structural rewrite complete
2017-09-12 Feature unit for headphones
2017-09-12 Move some small functions into feature units
2017-09-12 Feature unit for analog attenuation
2017-09-12 Mute only so that DAC volume will be used as the main volume
2017-09-12 Reduce audio buffering space, reduce audio latency
2017-09-12 Fix audio endpoint disabling
2017-09-13 Improve audio reliability, disable isochronous incomplete interrupt if not needed
2017-09-13 Use dedicated interrupt for endpoint 1 (audio)
2017-09-13 Move keyboard mismatch debugging output outside critical region
2017-09-22 Improve audio data rate feedback, reduce audio buffer size
2017-09-23 Keycode update using HID vendor-defined interface
2017-09-26 Update software version to 0x0004
2017-10-12 Initial README.md
2017-11-10 USB MSC initial
2017-11-10 USB fix for endpoint 0 halting control under debug
2017-11-10 Add USB mass storage interface in debug build
2017-11-19 KiCad PCB conversion initial
2017-12-17 Host/Qt: GUI application initial
2017-12-18 Host: Plugins
2017-12-18 host/plugins/ping: Correct header file definitions
2017-12-18 host/plugins/keycode: Keycode update
2017-12-18 host/plguins/keycode: Remove unsued parameter warning
2017-12-18 host: Support for MSVC 2017 compiler
2017-12-23 host/plugins/keycode: Keycode conversion from keyboard key press
2017-12-24 host/plugins/keycode: All keyboard usage IDs
2018-01-01 Add product name macro define
2018-01-01 debug: Flush stdout on debug breakpoints
2018-01-01 device/usb/msc/scsi: Vital product data: Unit serial number page
2018-01-01 device/usb/msc/scsi: READ CAPACITY (10)
2018-01-01 device/usb/msc/scsi: READ (10) initial
2018-01-01 device/usb/msc/scsi: Ignore SYNCHRONIZE CACHE (10)
2018-01-01 device/usb/msc/scsi: Ignore START STOP UNIT
2018-01-01 device/usb/msc/scsi: Simulate 64kiB RAM disk
2018-01-01 device/usb/msc/scsi: Improve command implementation check
2018-01-01 device/usb/msc/scsi: WRITE (10) initial
2018-01-01 device/usb/msc/scsi: Fix block write
2018-01-01 device/peripheral/mmc: Calculate card capacity
2018-01-01 device/peripheral/mmc: SCSI interface functions initial
2018-01-01 device/usb/msc: Check for MSC accessibility
2018-01-01 device: Add SD/MMC and USB MSC to release build
2018-01-02 device/peripheral/mmc: RX DMA initial
2018-01-02 device: Update CMSIS, use UID and FLASHSIZE from CMSIS
2018-01-02 device: Move heap to DTCM region for data cache
2018-01-02 device: Enable I-Cache and D-Cache
2018-01-02 device/vendor: Move report to DTCM for cache coherency
2018-01-02 device/debug: Improve panic message
2018-01-03 device/macros: Static assertion
2018-01-03 device/peripheral/mmc: TX DMA initial
2018-01-03 device/usb/msc: Double buffering
2018-01-03 device: Only show debug statistics when updated
2018-01-03 device/peripheral/mmc, device/usb/msc/scsi: Break apart write process, improve performance
2018-01-04 device/peripheral/mmc, device/usb/msc/scsi: Use DMA for both RX and TX
2018-01-04 device/clocks: Increase MCO1 GPIO speed
2018-01-04 device/peripheral/mmc, device/usb/msc: Start data transfer before read completion, improved performance
2018-01-04 device/usb: Add status return to IN endpoint transfer
2018-01-04 device/usb: Move endpoint initialisations after set configuration
2018-01-04 host/qt: Refresh device list on gaining window focus
2018-01-05 device/usb: Do not ignore IN endpoint data with NAKSTS set
2018-01-06 device/peripheral/audio: Sin wave for audio testing
2018-01-07 device: Show USB RAM usage for debugging
2018-01-07 device/usb/audio2: Support for multi-packet transfer
2018-01-07 device/usb: Fix USB RAM allocation start address issue
2018-01-07 device: Remove audio test key, since UAC2 now works with MSC
2018-01-07 device/clocks: Add timer clock frequency calculations
2018-01-07 device/peripheral/rgb: RGB and scan timer hierarchy initial
2018-01-08 device/vendor: RGB set descriptor initial
2018-01-08 device/clocks: Add DCKCFGR1 to timer clock frequency calculation
2018-01-08 device/vendor: Update report formats for RGB LED support
2018-01-08 device/vendor: Fix LED config packet size check and RGB ordering
2018-01-08 host/plugins/led: LED configuration plugin
2018-01-08 device/peripheral/led: Fix intensity precision issue
2018-01-08 device/peripheral/audio: Faster recovery from lost sync
2018-01-08 device/usb/msc/scsi: Use block as address and length unit
2018-01-08 device: More escape sequences
2018-01-08 device/peripheral/mmc: Hot plug support initial
2018-01-08 device/peripheral: Miscellaneous
2018-01-09 device/peripheral/mmc: Status report for interrupted read/write operations
2018-01-09 device/usb/msc: Support for hot plug during write operations
2018-01-09 device/peripheral/mmc: Improve hot plug stability
2018-01-09 device: Split main and bootloader projects
2018-01-09 device/peripheral/mmc: Use weak alias for SCSI functions
2018-01-10 device/usb: Fixed a bug when host requested a 64-byte descriptor
2018-01-10 device/flash_scsi: SCSI interface flash operations initial
2018-01-10 device/FatFs: Rename SD to MMC
2018-01-10 device/usb/msc/scsi: Support for different product names
2018-01-10 device: Use flash partitions as SCSI & FatFs devices initial
2018-01-10 device/usb/msc/scsi: Add removable as device type
2018-01-10 device: Directory structure update
2018-01-10 device/usb/msc: Fix potential cacheing issue with data prefetch
2018-01-10 device/usb/msc: Instead of flushing cache, use DTCM section
2018-01-10 device: Attach shadow configuration partition to main
2018-01-11 PCB: New revision (v0.4) inital
2018-01-12 PCB: Revision 1.0, silkscreen checked
2018-01-13 PCB: Move a few things around (power supply rails)
2018-01-13 device: Miscellaneous fixes for release build
2018-01-13 device/usb/msc: Improve performance by storing the currently active LUN
2018-01-21 device/logic/vendor: I2C control initial
2018-01-21 device/peripheral/audio: Proper audio reset
2018-01-21 host/plugins/i2c: Handle return presses
2018-01-23 pcb: Corrections to BOM
2018-01-23 device/peripheral/keyboard: Support for PCB revision 1.0
2018-01-23 device/peripheral/mmc: Support for PCB revision 1.0
2018-01-23 device/peripheral/led: Support for PCB revision 1.0
2018-01-26 device/peripheral/keyboard: Add #define keyboard masks
2018-01-27 device/logic/led_trigger: Trigger implementation initial
2018-01-28 device/logic/led_trigger: Multiple evaluation channel support
2018-01-28 device/logic/led_trigger: Use floating point numbers for colour normalisation
2018-01-31 device/ld: Update linker scripts to bootloader + app layout
2018-02-01 device: Miscellaneous optimisation for bootloader
2018-02-01 device/system/flash: Miscellaneous fixes and stability improvements
2018-02-01 device/peripheral/led: Structural update, support for PCB revision 0.2
2018-02-01 device: Miscellaneous performance improvements
2018-02-02 device: Try new qbs project structure
2018-02-03 device/peripheral/audio, device/usb/audio2/usb_audio2: Skip UAC2 initialisation if audio codec was not found
2018-02-04 device/peripheral/mpu: MPU9250 initial
2018-02-05 device/peripheral/i2c: Generalise I2C & DMA base addresses
2018-02-05 device/peripheral/i2c: Interrupt mode read & write operations
2018-02-05 device/peripheral/i2c: Miscellaneous improvements
2018-02-06 device/peripheral/i2c: Add register address as a parameter to i2c_write
2018-02-07 device/peripheral/audio: Multi-byte I2C transfer for configuration updates
2018-02-08 device/peripheral/i2c: Support for TX DMA & non-blocking write
2018-02-08 device/peripheral/audio: Do not register UAC if codec not found
2018-02-09 device/peripheral/mpu: Connect MPU to USB HID joystick
2018-02-09 device/usb/hid/joystick: Add 5 buttons
2018-02-10 device/peripheral/mpu: Miscellaneous
2018-02-11 device/peripheral/mpu: Sample update counter
2018-02-12 device/peripheral/mmc: Use double buffering for read
2018-02-12 device/peripheral/i2c: Miscellaneous
2018-02-12 device/peripheral/mmc: Multiple read buffers
2018-02-13 device/logic/scsi: Output potential data before read complete
2018-02-13 device/peripheral/mmc: Combine continuous buffer space
2018-02-13 device/peripheral/mmc: Multi-block transfer
2018-02-14 device/system_stm32f7xx: Improve fault debugging output
2018-02-14 device/system_stm32f7xx: Separate hard fault handler
2018-02-15 device: Fix occasional crash from memory allocation
2018-02-15 device: Update CMSIS
2018-02-17 device/api: Change logic/vendor to api, initial support for configuration channels
2018-02-17 Move device/logic/api_proc to device/api/api_proc
2018-02-17 host: Miscellaneous
2018-02-17 device/api/api_led: RGB LED configuration API
2018-02-18 host: Plugin version check
2018-02-18 host/plugins/i2c: Support for newer implementation
2018-02-19 device/peripheral/keyboard: Get keycode and key names
2018-02-19 host/plugins/keycode: Key code read back
2018-02-19 host/plugins/led: Use payload size to determine operation
2018-02-19 host/console, host/plugins/info: Payload size of 0 as channel count report
2018-02-20 device/api/api_config: System configurations initial, keyboard & joystick update enable
2018-02-20 device/api/api_config: Connect/disconnect MicroSD & Flash
2018-02-22 device/usb/hid/mouse: USB HID mouse initial
2018-02-22 device/peripheral/mpu: Gyroscope minimal integration implementation
2018-02-23 device/motion_driver/core/driver/eMPL: Port driver to device
2018-02-23 device/peripheral/mpu: Initial test for motion_driver
2018-02-23 device/peripheral/mpu: Non-blocking FIFO packet read
2018-02-23 host/plugins/motion: Render device orientation from quaternion report
2018-02-23 device/peripheral/mpu: Report accelerometer & gyroscope values
2018-02-23 host/plugins/plugin: OUT report retry
2018-02-23 host/plugins/motion: Option to disable updating 3D model
2018-02-24 device/eMPL: Parse compass data from existing register content
2018-02-24 device/api/api_motion: Report compass data
2018-02-25 device/peripheral/mpu: Add axes orientation correction
2018-02-25 host/plugins/motion: Show top view
2018-02-25 host/plugins/motion: Use vertex array objects
2019-03-05 PCB version 1.1 connected
2019-03-12 PCB with silkscreen
2019-04-09 Restart project, because why not
2019-04-11 Use link time list to store event handlers
2019-04-15 Update PCB BOM, fix miscellaneous schematic markings
2019-04-15 USB endpoint reservation initial
2019-04-24 PCB revision 1.2, fix RGB LED footprint
2019-11-08 Initial common files
2019-11-09 USB enumeration initial
2019-11-10 Better implementation of link time list
2019-12-23 PCB revision 1.3 with USB Type-C, more datasheets
2020-01-15 USB OUT initial
2020-04-27 USB configuration descriptor done
2020-04-27 device: USB HID keyboard initial
2020-04-27 USB HID vendor initial
2020-04-28 device: Use -O3 for memory test
2020-04-28 device: Memory test repeat 4 times

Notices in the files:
Src/main.c:
COPYRIGHT(c) 2016 STMicroelectronics
(C) COPYRIGHT STMicroelectronics *****END OF FILE
parts and their libraries:
Wurth_Elektronik_Electromechanic_Input-O: Copyright: Würth Elektronik
SparkFun-Sensors: Licensing: Creative Commons ShareAlike 4.0 International - https://creativecommons.org/licenses/by-sa/4.0
